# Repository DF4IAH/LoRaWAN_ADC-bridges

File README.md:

# LoRaWAN_ADC-bridges
MCU board as __LoRaWAN TTN device__  for multiple electronic scales.

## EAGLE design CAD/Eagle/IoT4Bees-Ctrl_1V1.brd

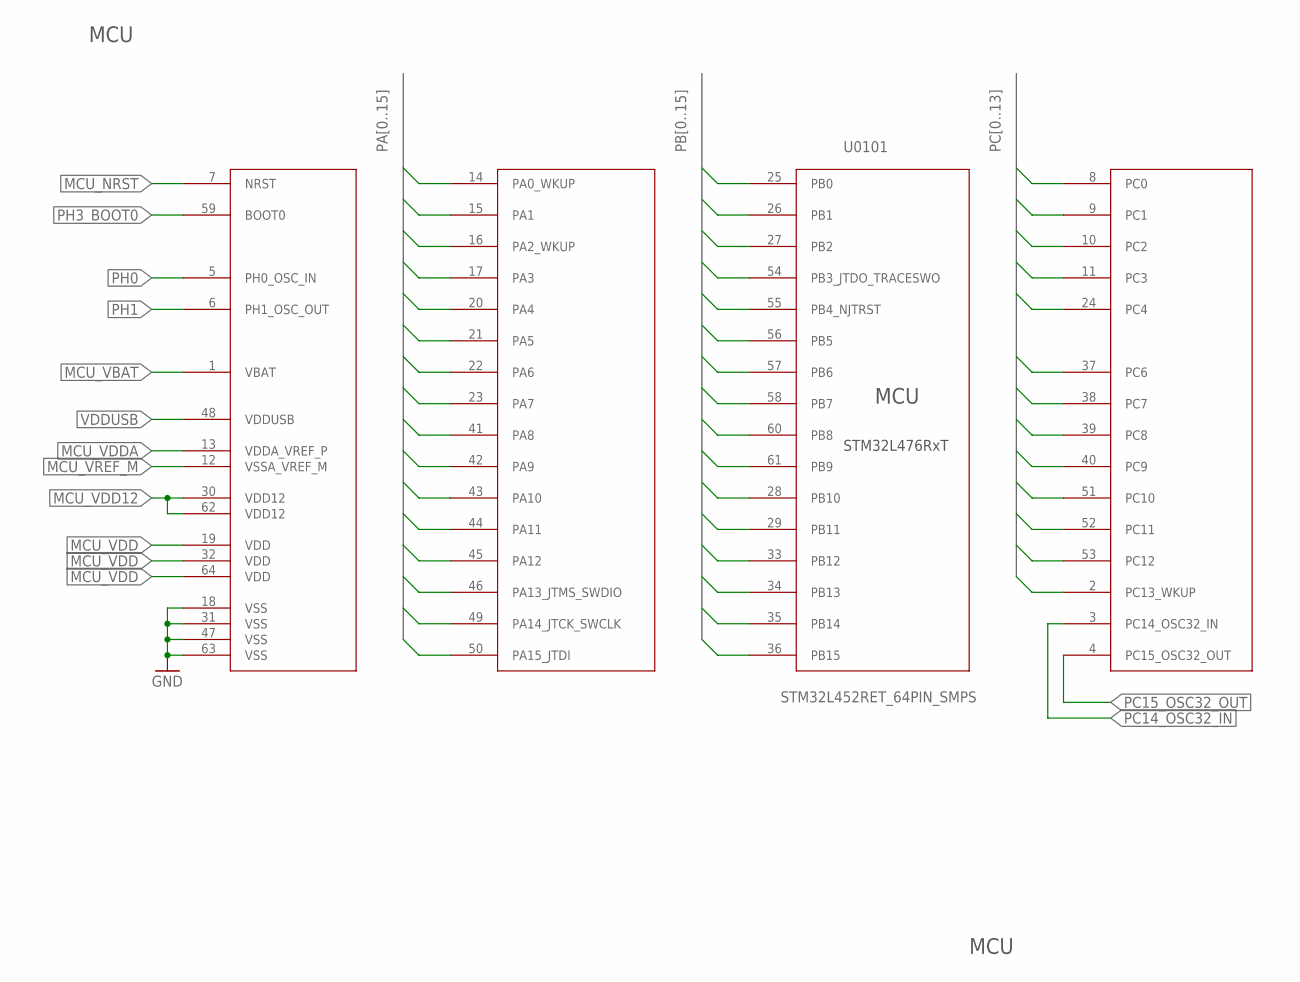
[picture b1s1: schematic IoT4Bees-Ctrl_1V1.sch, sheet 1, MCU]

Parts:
U0101: STM32L452RET_64PIN_SMPS; LQFP64

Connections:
GND: U0101.18 (VSS), U0101.31 (VSS), U0101.47 (VSS), U0101.63 (VSS); also elsewhere on the board
MCU_NRST: U0101.7 (NRST); also elsewhere on the board
MCU_VBAT: U0101.1 (VBAT); also elsewhere on the board
MCU_VDD: U0101.19 (VDD), U0101.32 (VDD), U0101.64 (VDD); also elsewhere on the board
MCU_VDD12: U0101.30 (VDD12), U0101.62 (VDD12); also elsewhere on the board
MCU_VDDA: U0101.13 (VDDA_VREF_P); also elsewhere on the board
MCU_VREF_M: U0101.12 (VSSA_VREF_M); also elsewhere on the board
PA0: U0101.14 (PA0_WKUP); also elsewhere on the board
PA1: U0101.15 (PA1); also elsewhere on the board
PA2: U0101.16 (PA2_WKUP); also elsewhere on the board
PA3: U0101.17 (PA3)
PA4: U0101.20 (PA4); also elsewhere on the board
PA5: U0101.21 (PA5); also elsewhere on the board
PA6: U0101.22 (PA6); also elsewhere on the board
PA7: U0101.23 (PA7); also elsewhere on the board
PA8: U0101.41 (PA8); also elsewhere on the board
PA9: U0101.42 (PA9); also elsewhere on the board
PA10: U0101.43 (PA10); also elsewhere on the board
PA11: U0101.44 (PA11); also elsewhere on the board
PA12: U0101.45 (PA12); also elsewhere on the board
PA13: U0101.46 (PA13_JTMS_SWDIO); also elsewhere on the board
PA14: U0101.49 (PA14_JTCK_SWCLK); also elsewhere on the board
PA15: U0101.50 (PA15_JTDI)
PB0: U0101.25 (PB0)
PB1: U0101.26 (PB1); also elsewhere on the board
PB2: U0101.27 (PB2)
PB3: U0101.54 (PB3_JTDO_TRACESWO)
PB4: U0101.55 (PB4_NJTRST)
PB5: U0101.56 (PB5); also elsewhere on the board
PB6: U0101.57 (PB6); also elsewhere on the board
PB7: U0101.58 (PB7); also elsewhere on the board
PB8: U0101.60 (PB8); also elsewhere on the board
PB9: U0101.61 (PB9)
PB10: U0101.28 (PB10); also elsewhere on the board
PB11: U0101.29 (PB11); also elsewhere on the board
PB12: U0101.33 (PB12); also elsewhere on the board
PB13: U0101.34 (PB13); also elsewhere on the board
PB14: U0101.35 (PB14); also elsewhere on the board
PB15: U0101.36 (PB15); also elsewhere on the board
PC0: U0101.8 (PC0); also elsewhere on the board
PC1: U0101.9 (PC1); also elsewhere on the board
PC2: U0101.10 (PC2); also elsewhere on the board
PC3: U0101.11 (PC3); also elsewhere on the board
PC4: U0101.24 (PC4); also elsewhere on the board
PC6: U0101.37 (PC6)
PC7: U0101.38 (PC7); also elsewhere on the board
PC8: U0101.39 (PC8); also elsewhere on the board
PC9: U0101.40 (PC9); also elsewhere on the board
PC10: U0101.51 (PC10); also elsewhere on the board
PC11: U0101.52 (PC11); also elsewhere on the board
PC12: U0101.53 (PC12); also elsewhere on the board
PC13: U0101.2 (PC13_WKUP); also elsewhere on the board
PC14_OSC32_IN: U0101.3 (PC14_OSC32_IN); also elsewhere on the board
PC15_OSC32_OUT: U0101.4 (PC15_OSC32_OUT); also elsewhere on the board
PH0: U0101.5 (PH0_OSC_IN); also elsewhere on the board
PH1: U0101.6 (PH1_OSC_OUT); also elsewhere on the board
PH3_BOOT0: U0101.59 (BOOT0); also elsewhere on the board
VDDUSB: U0101.48 (VDDUSB); also elsewhere on the board

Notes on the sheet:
STM32L476RxT
MCU

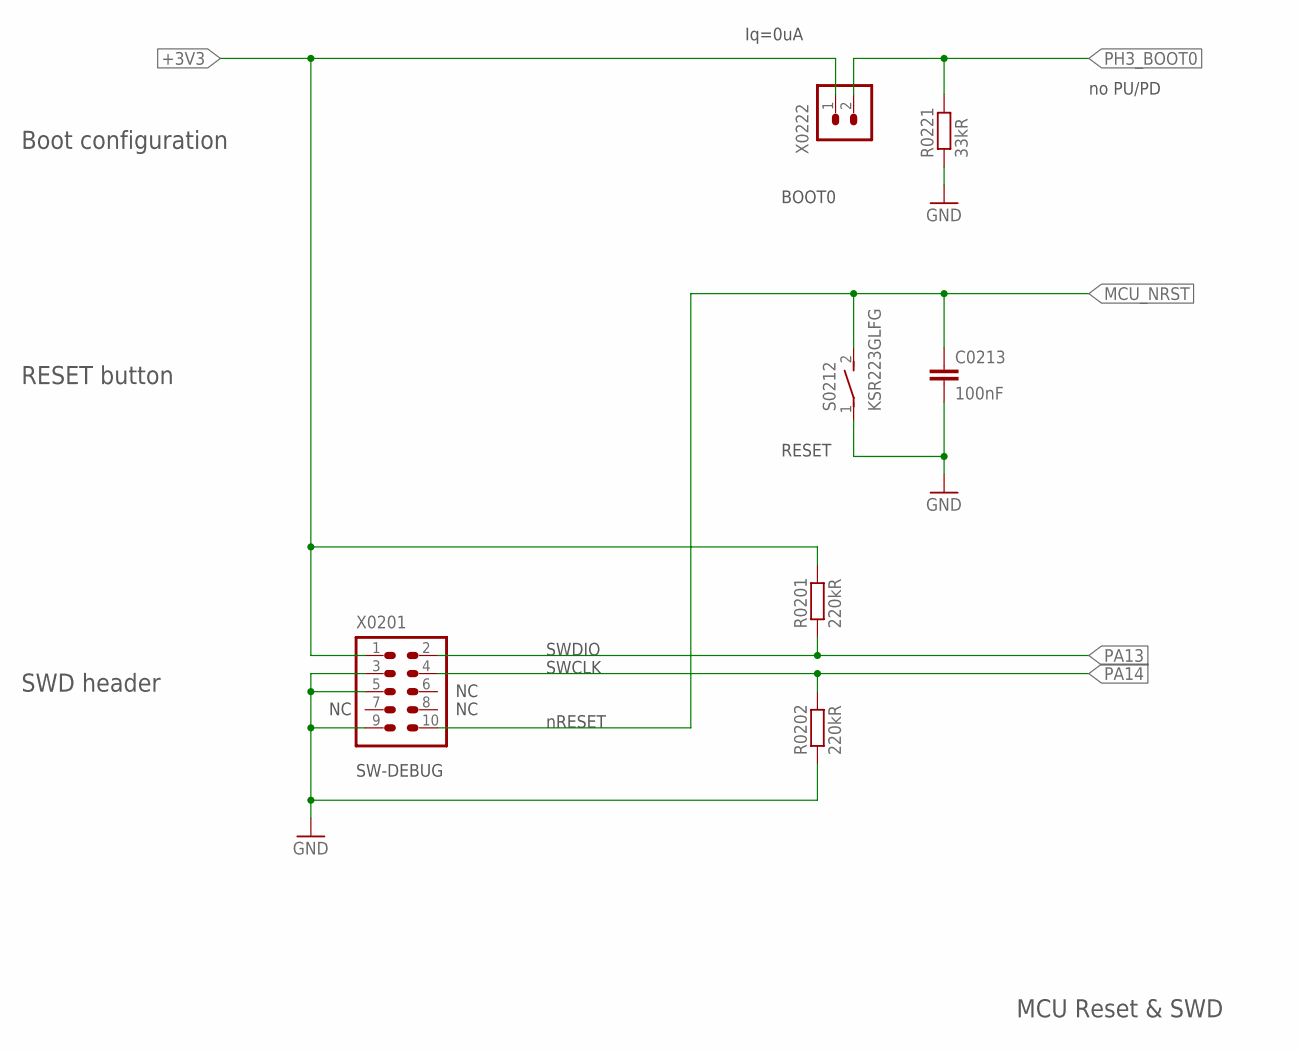
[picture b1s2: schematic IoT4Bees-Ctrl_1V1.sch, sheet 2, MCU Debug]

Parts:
C0213: 100nF; C0402
R0201, R0202: 220kR; R0402
R0221: 33kR; R0402
S0212: KSR223GLFG; KSR223G_SMD_1POL
X0201: FTSH-105-01-F-D-K; 2X05_1MM27_SHROUDED_CORTEX_JTAG_SWD
X0222: HEADER-1X2; 1X02

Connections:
+3V3: R0201.2, X0201.1, X0222.1; also elsewhere on the board
GND: C0213.2, R0202.1, R0221.1, S0212.1, X0201.3, X0201.5, X0201.9; also elsewhere on the board
MCU_NRST: C0213.1, S0212.2 (S), X0201.10; also elsewhere on the board
PA13: R0201.1, X0201.2; also elsewhere on the board
PA14: R0202.2, X0201.4; also elsewhere on the board
PH3_BOOT0: R0221.2, X0222.2; also elsewhere on the board

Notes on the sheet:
SWDIO
SWCLK
RESET
BOOT0
SW-DEBUG
SWD header
Boot configuration
RESET button
nRESET
MCU Reset & SWD
no PU/PD
Iq=0uA

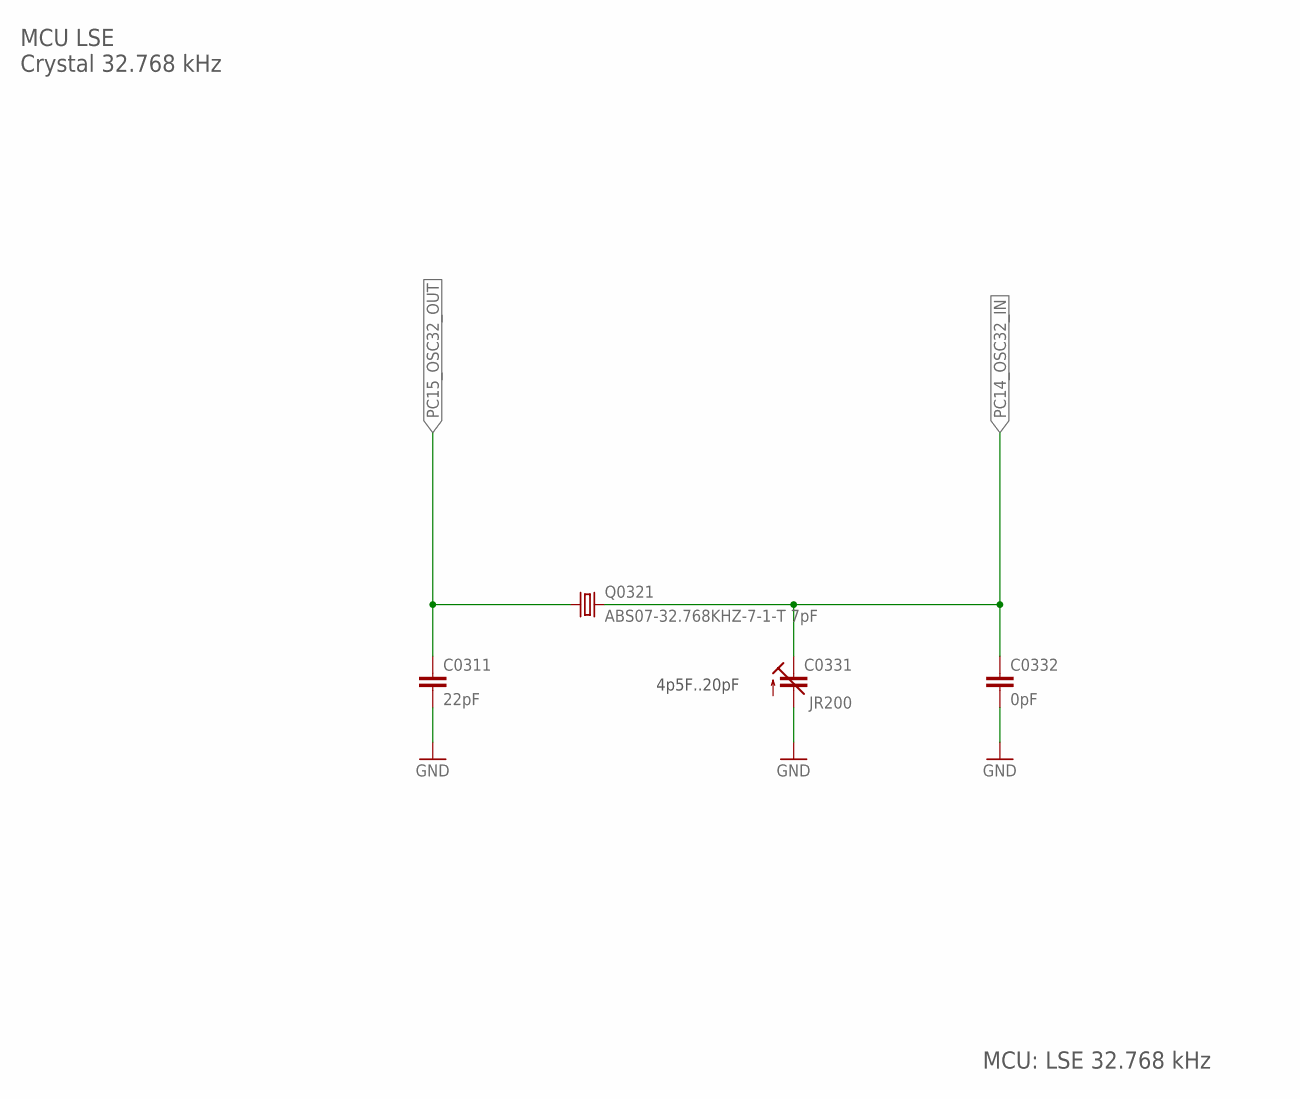
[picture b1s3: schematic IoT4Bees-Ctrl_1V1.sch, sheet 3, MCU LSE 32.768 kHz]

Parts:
C0311: 22pF; C0402
C0331: JR200; 3MM2_X_2MM5
C0332: 0pF; C0402
Q0321: ABS07-32.768KHZ-7-1-T 7pF; ABS07

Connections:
GND: C0311.2, C0331.+ (A), C0332.2; also elsewhere on the board
PC14_OSC32_IN: C0331.- (E), C0332.1, Q0321.2; also elsewhere on the board
PC15_OSC32_OUT: C0311.1, Q0321.1; also elsewhere on the board

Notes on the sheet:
4p5F..20pF
MCU LSE Crystal 32.768 kHz
MCU: LSE 32.768 kHz

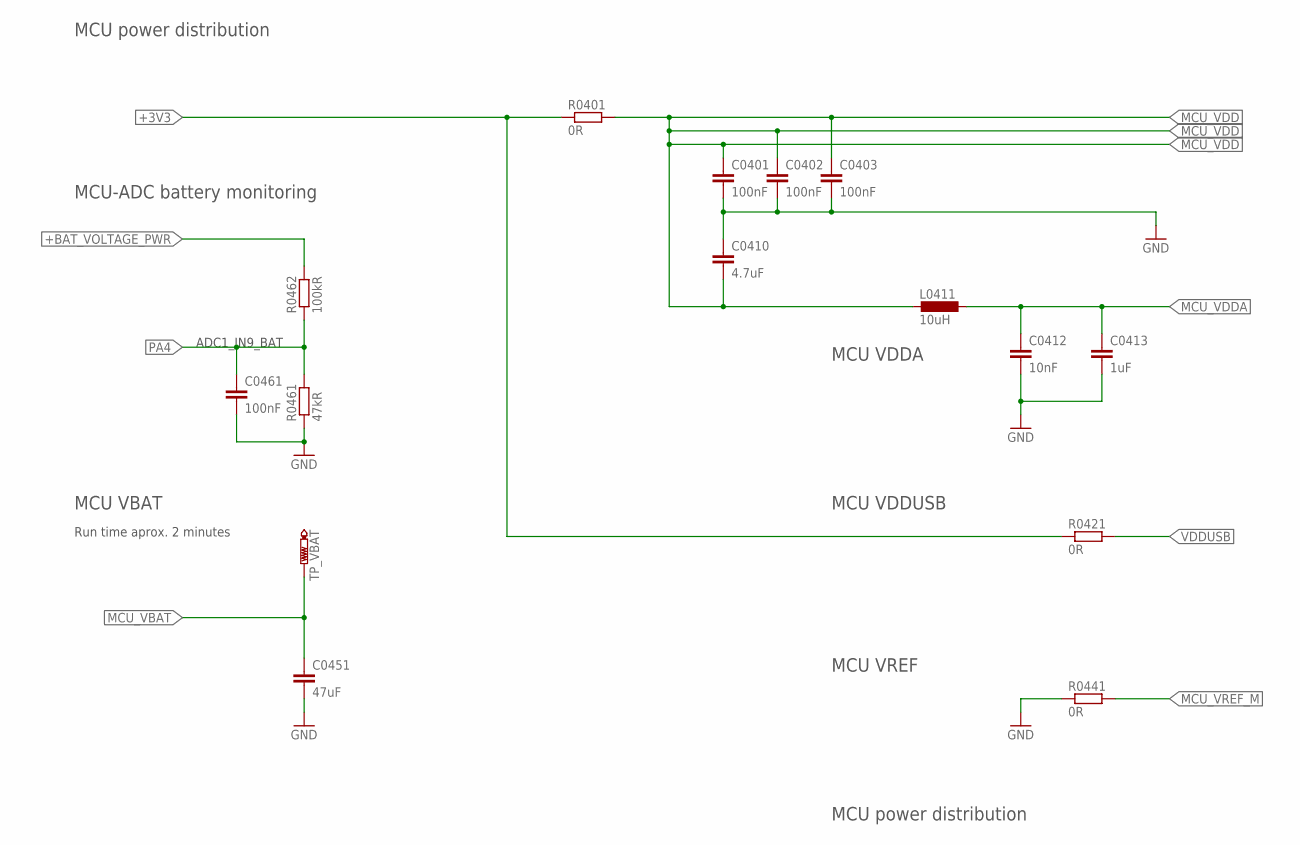
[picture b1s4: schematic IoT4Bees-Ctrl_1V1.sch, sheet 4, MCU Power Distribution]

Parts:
C0401, C0402, C0403, C0461: 100nF; C0402
C0410: 4.7uF; C0603
C0412: 10nF; C0402
C0413: 1uF; C0402
C0451: 47uF; C0805
L0411: 10uH; L0603
R0401, R0421, R0441: 0R; R0402
R0461: 47kR; R0402
R0462: 100kR; R0402
TP_VBAT: PTR1TP06R; TP06R

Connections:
+3V3: R0401.1, R0421.1; also elsewhere on the board
+BAT_VOLTAGE_PWR: R0462.2; also elsewhere on the board
GND: C0401.2, C0402.2, C0403.2, C0410.1, C0412.2, C0413.2, C0451.2, C0461.2, R0441.1, R0461.1; also elsewhere on the board
MCU_VBAT: C0451.1, TP_VBAT.TP; also elsewhere on the board
MCU_VDD: C0401.1, C0402.1, C0403.1, C0410.2, L0411.1, R0401.2; also elsewhere on the board
MCU_VDDA: C0412.1, C0413.1, L0411.2; also elsewhere on the board
MCU_VREF_M: R0441.2; also elsewhere on the board
PA4: C0461.1, R0461.2, R0462.1; also elsewhere on the board
VDDUSB: R0421.2; also elsewhere on the board

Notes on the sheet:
MCU VDDA
MCU VREF
MCU VBAT
MCU power distribution
Run time aprox. 2 minutes
ADC1_IN9_BAT
MCU-ADC battery monitoring
MCU VDDUSB

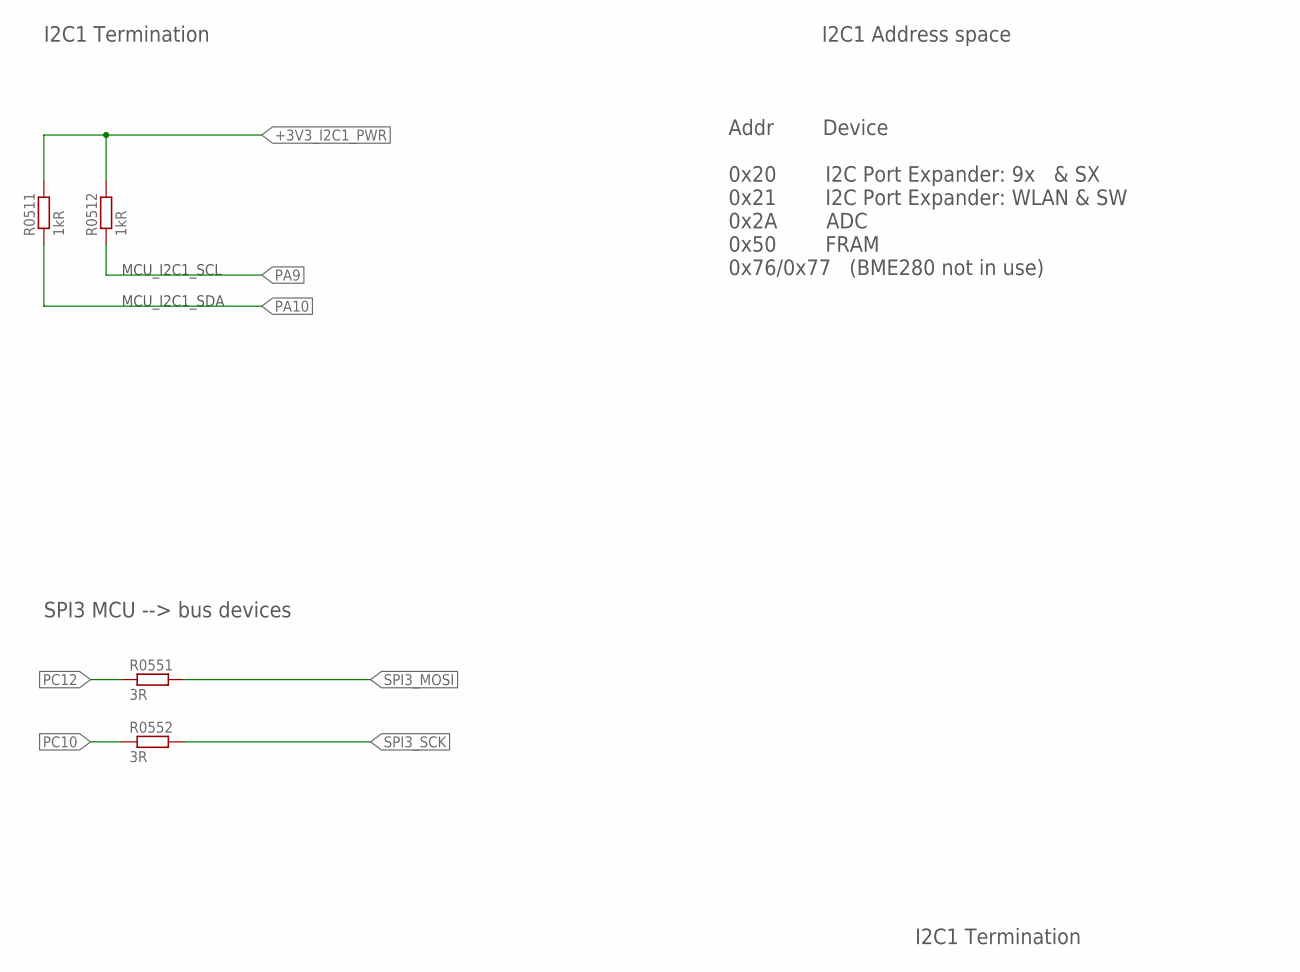
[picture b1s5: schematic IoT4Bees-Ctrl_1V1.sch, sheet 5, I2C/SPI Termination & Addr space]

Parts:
R0511, R0512: 1kR; R0402
R0551, R0552: 3R; R0402

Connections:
+3V3_I2C1_PWR: R0511.2, R0512.2; also elsewhere on the board
PA9: R0512.1; also elsewhere on the board
PA10: R0511.1; also elsewhere on the board
PC10: R0552.1; also elsewhere on the board
PC12: R0551.1; also elsewhere on the board
SPI3_MOSI: R0551.2; also elsewhere on the board
SPI3_SCK: R0552.2; also elsewhere on the board

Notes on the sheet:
Addr Device 0x20 I2C Port Expander: 9x & SX 0x21 I2C Port Expander: WLAN & SW 0x2A ADC 0x50 FRAM 0x76/0x77 (BME280 not in use)
I2C1 Termination
I2C1 Address space
MCU_I2C1_SCL
MCU_I2C1_SDA
SPI3 MCU --> bus devices

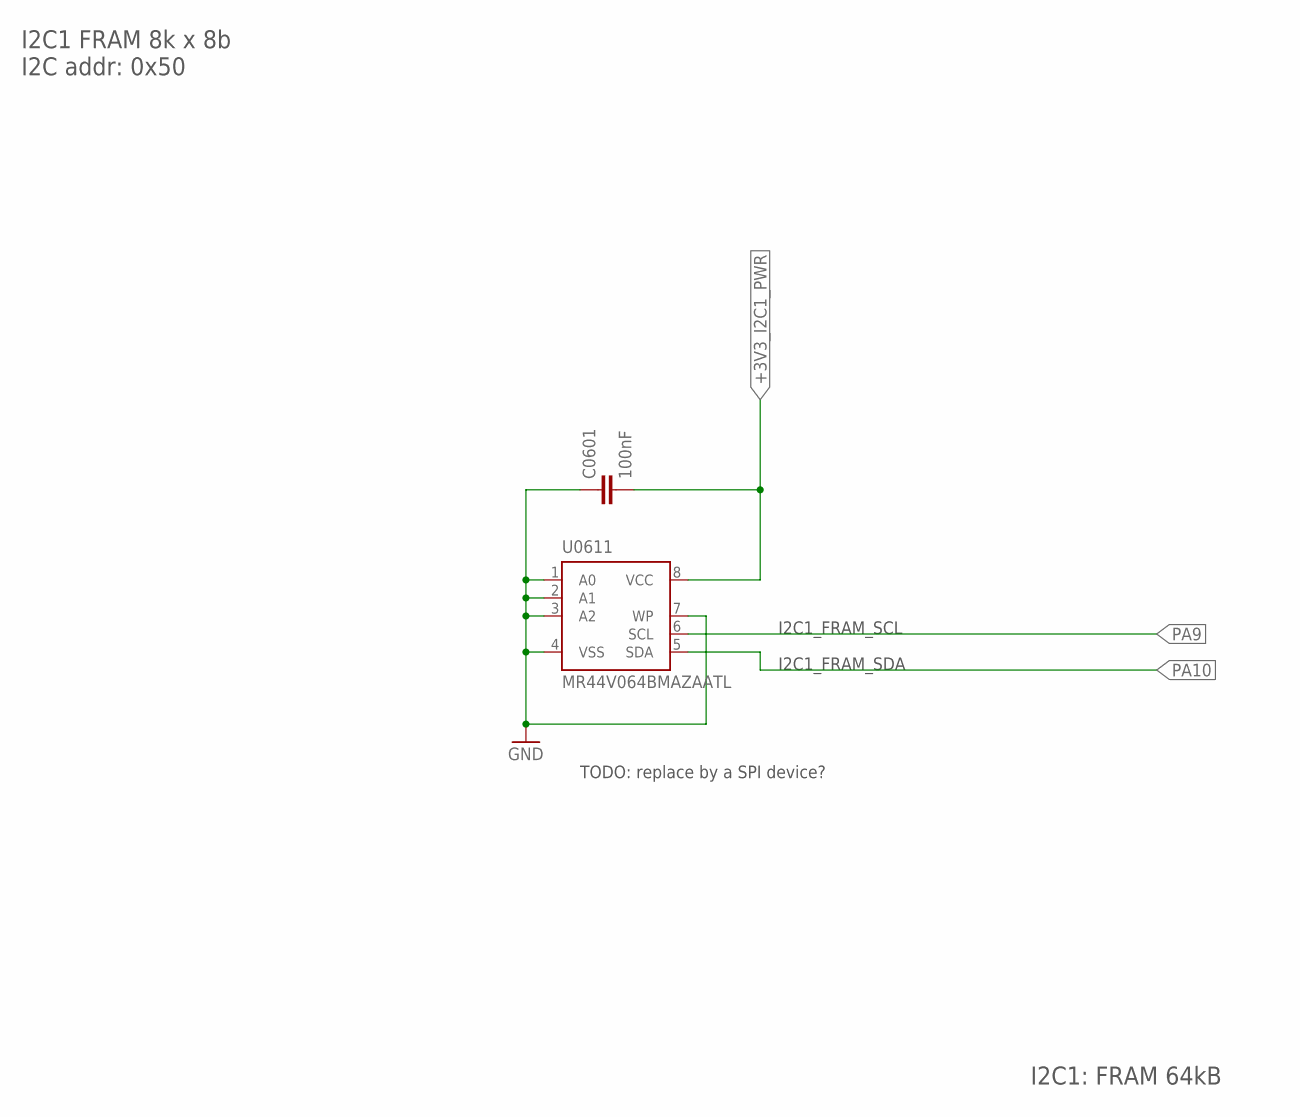
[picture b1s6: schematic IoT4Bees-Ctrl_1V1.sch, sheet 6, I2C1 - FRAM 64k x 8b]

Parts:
C0601: 100nF; C0402
U0611: MR44V064BMAZAATL; SOIC8_150MIL

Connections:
+3V3_I2C1_PWR: C0601.2, U0611.8 (VCC); also elsewhere on the board
GND: C0601.1, U0611.1 (A0), U0611.2 (A1), U0611.3 (A2), U0611.4 (VSS), U0611.7 (WP); also elsewhere on the board
PA9: U0611.6 (SCL); also elsewhere on the board
PA10: U0611.5 (SDA); also elsewhere on the board

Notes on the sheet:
I2C1: FRAM 64kB
I2C1 FRAM 8k x 8b I2C addr: 0x50
I2C1_FRAM_SCL
I2C1_FRAM_SDA
TODO: replace by a SPI device?

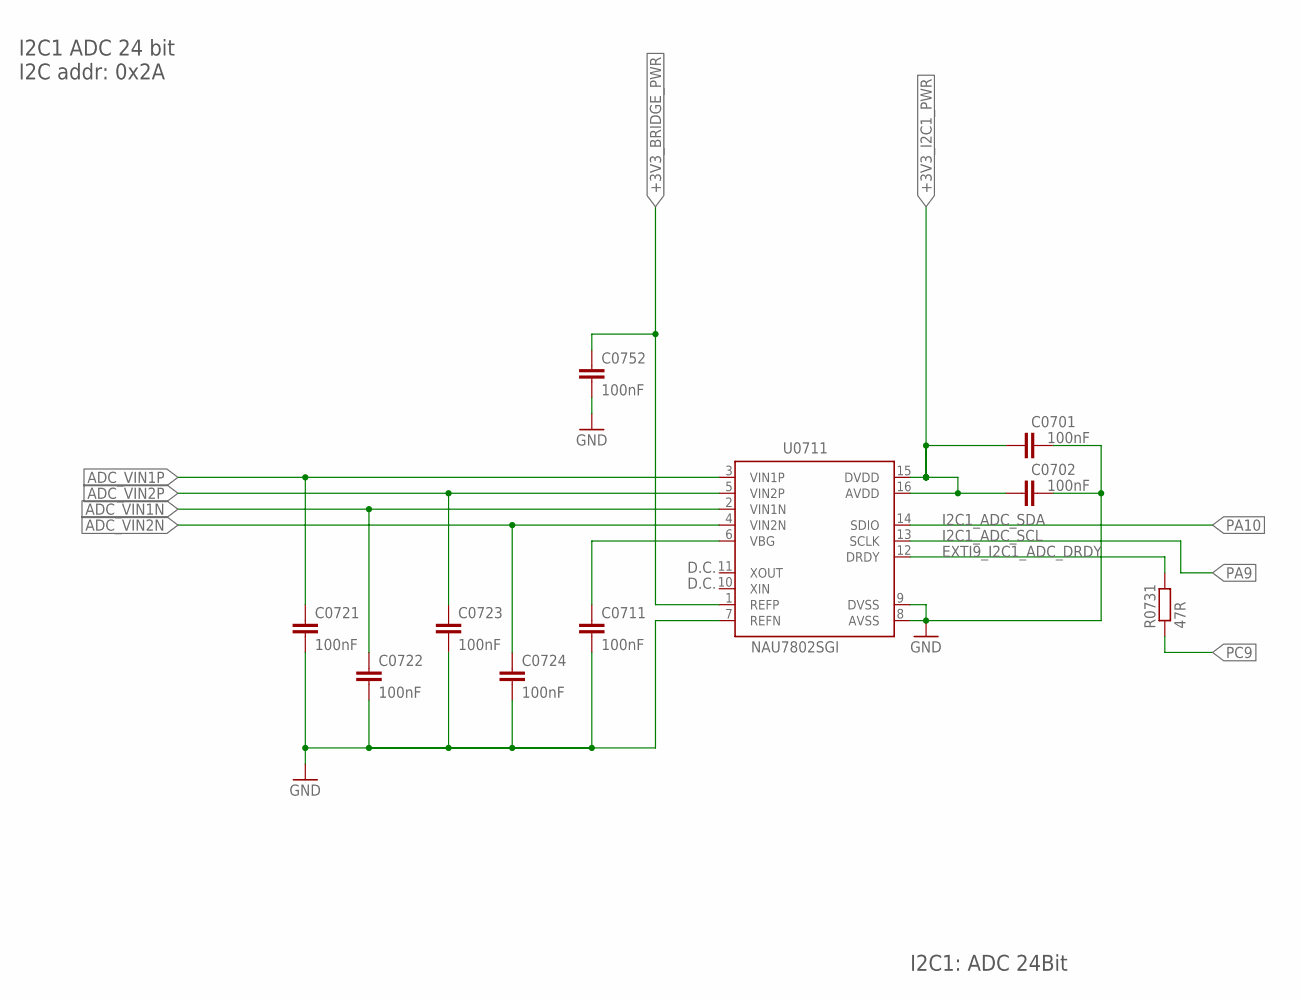
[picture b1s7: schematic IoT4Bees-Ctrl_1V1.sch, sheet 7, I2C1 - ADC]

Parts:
C0701, C0702, C0711, C0721, C0722, C0723, C0724, C0752: 100nF; C0402
R0731: 47R; R0402
U0711: NAU7802SGI; LSOP16

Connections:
+3V3_BRIDGE_PWR: C0752.1, U0711.1 (REFP); also elsewhere on the board
+3V3_I2C1_PWR: C0701.1, C0702.1, U0711.15 (DVDD), U0711.16 (AVDD); also elsewhere on the board
ADC_VBG: C0711.1, U0711.6 (VBG)
ADC_VIN1N: C0722.1, U0711.2 (VIN1N); also elsewhere on the board
ADC_VIN1P: C0721.1, U0711.3 (VIN1P); also elsewhere on the board
ADC_VIN2N: C0724.1, U0711.4 (VIN2N); also elsewhere on the board
ADC_VIN2P: C0723.1, U0711.5 (VIN2P); also elsewhere on the board
EXTI9_I2C1_ADC_DRDY: R0731.2, U0711.12 (DRDY)
GND: C0701.2, C0702.2, C0711.2, C0721.2, C0722.2, C0723.2, C0724.2, C0752.2, U0711.7 (REFN), U0711.8 (AVSS), U0711.9 (DVSS); also elsewhere on the board
PA9: U0711.13 (SCLK); also elsewhere on the board
PA10: U0711.14 (SDIO); also elsewhere on the board
PC9: R0731.1; also elsewhere on the board

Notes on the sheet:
I2C1: ADC 24Bit
I2C1 ADC 24 bit I2C addr: 0x2A
I2C1_ADC_SDA
I2C1_ADC_SCL
D.C.

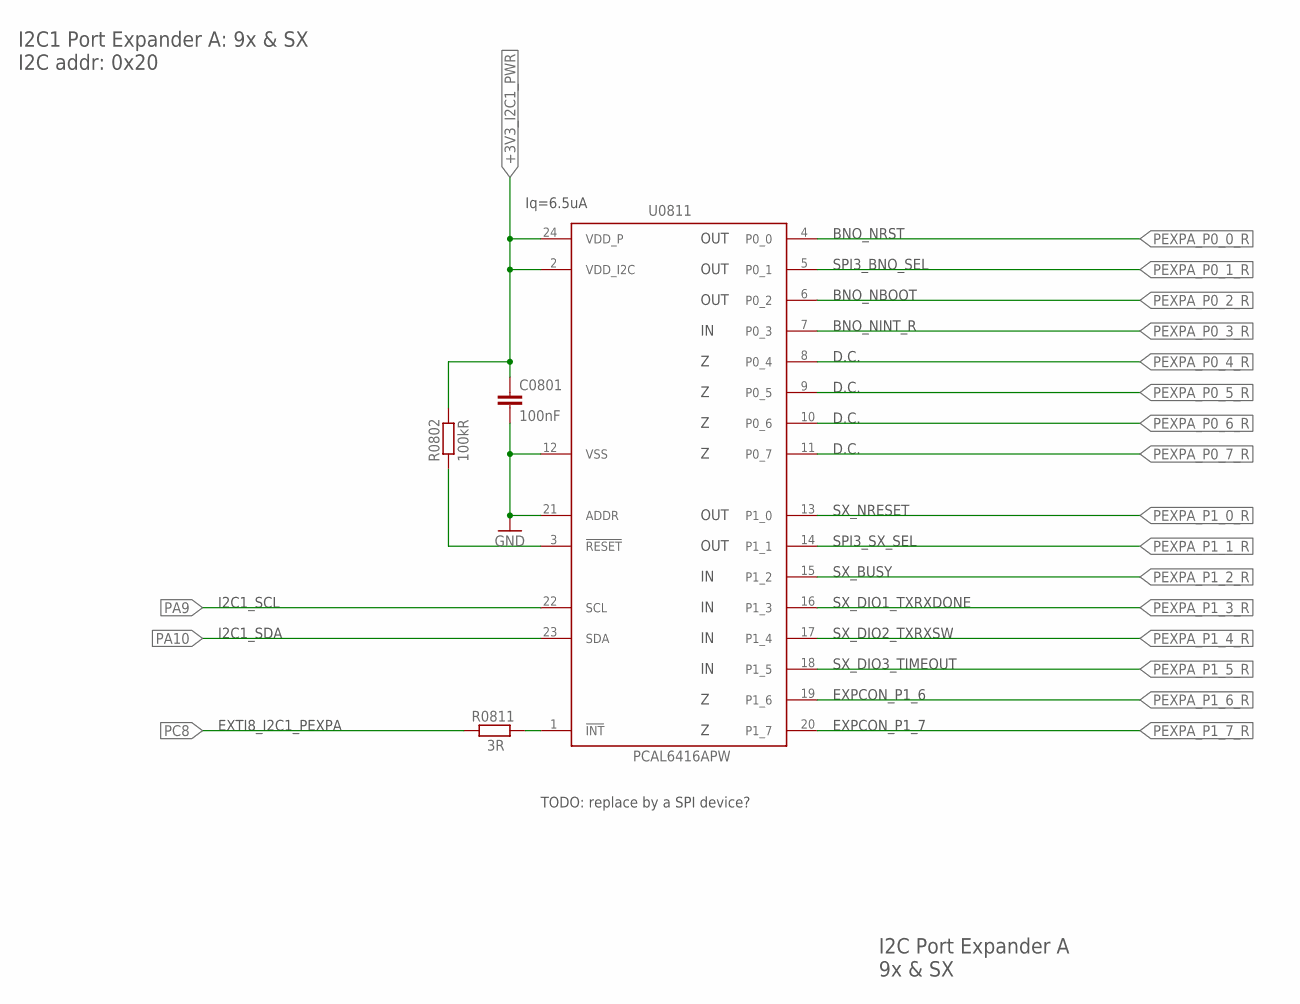
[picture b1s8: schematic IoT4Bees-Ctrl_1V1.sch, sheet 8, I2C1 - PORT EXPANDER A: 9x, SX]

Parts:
C0801: 100nF; C0402
R0802: 100kR; R0402
R0811: 3R; R0402
U0811: PCAL6416APW; TSSOP24_SOT355-1

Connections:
+3V3_I2C1_PWR: C0801.1, R0802.2, U0811.2 (VDD_I2C), U0811.24 (VDD_P); also elsewhere on the board
GND: C0801.2, U0811.12 (VSS), U0811.21 (ADDR); also elsewhere on the board
PA9: U0811.22 (SCL); also elsewhere on the board
PA10: U0811.23 (SDA); also elsewhere on the board
PC8: R0811.1; also elsewhere on the board
PEXPA_INTN: R0811.2, U0811.1 (!INT)
PEXPA_P0_0_R: U0811.4 (P0_0); also elsewhere on the board
PEXPA_P0_1_R: U0811.5 (P0_1); also elsewhere on the board
PEXPA_P0_2_R: U0811.6 (P0_2); also elsewhere on the board
PEXPA_P0_3_R: U0811.7 (P0_3); also elsewhere on the board
PEXPA_P0_4_R: U0811.8 (P0_4)
PEXPA_P0_5_R: U0811.9 (P0_5)
PEXPA_P0_6_R: U0811.10 (P0_6)
PEXPA_P0_7_R: U0811.11 (P0_7)
PEXPA_P1_0_R: U0811.13 (P1_0); also elsewhere on the board
PEXPA_P1_1_R: U0811.14 (P1_1); also elsewhere on the board
PEXPA_P1_2_R: U0811.15 (P1_2); also elsewhere on the board
PEXPA_P1_3_R: U0811.16 (P1_3); also elsewhere on the board
PEXPA_P1_4_R: U0811.17 (P1_4); also elsewhere on the board
PEXPA_P1_5_R: U0811.18 (P1_5); also elsewhere on the board
PEXPA_P1_6_R: U0811.19 (P1_6); also elsewhere on the board
PEXPA_P1_7_R: U0811.20 (P1_7); also elsewhere on the board
PEXPA_RESET: R0802.1, U0811.3 (!RESET)

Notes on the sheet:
I2C Port Expander A 9x & SX
I2C1 Port Expander A: 9x & SX I2C addr: 0x20
Iq=6.5uA
EXTI8_I2C1_PEXPA
D.C.
OUT
BNO_NRST
BNO_NBOOT
SPI3_BNO_SEL
BNO_NINT_R
SX_BUSY
SX_NRESET
SPI3_SX_SEL
SX_DIO3_TIMEOUT
SX_DIO2_TXRXSW
SX_DIO1_TXRXDONE
EXPCON_P1_6
I2C1_SCL
I2C1_SDA
EXPCON_P1_7
TODO: replace by a SPI device?

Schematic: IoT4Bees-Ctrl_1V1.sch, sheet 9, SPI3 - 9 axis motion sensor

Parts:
C0901, C0902, C0903: 100nF; C0402
C0921, C0922: 22pF; C0402
D0901: CMAD6001; SOD923
Q0921: ABS07-32.768KHZ; ABS07
R0901, R0902, R0904: 3R; R0402
R0903: 47R; R0402
R0931, R0932: 3.9kR; R0402
U0911: BNO085; BNO085_LGA28

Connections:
+3V3_SPI3_PWR: C0901.1, C0902.1, R0931.2, R0932.2, U0911.3 (VDD), U0911.5 (PS1), U0911.28 (VDDIO); also elsewhere on the board
BNO085_PS0_WAKE_R: D0901.A, R0903.1
BNO_CAP: C0903.1, U0911.9 (CAP)
BNO_CLKSEL1_XOUT32: C0922.1, Q0921.1, U0911.26 (CLKSEL1/XOUT32)
BNO_ENV_SCL: R0932.1, U0911.15 (ENV_SCL)
BNO_ENV_SDA: R0931.1, U0911.16 (ENV_SDA)
BNO_H_CSN: R0904.2, U0911.18 (H_CSN)
BNO_INTN: R0902.2, U0911.14 (H_INTN)
BNO_MISO: R0901.2, U0911.20 (H_SDA/MISO/TX)
BNO_PS0_WAKE: R0903.2, U0911.6 (PS0/WAKE)
BNO_XIN32: C0921.1, Q0921.2, U0911.27 (XIN32)
GND: C0901.2, C0902.2, C0903.2, C0921.2, C0922.2, U0911.2 (VSS), U0911.10 (CLKSEL0), U0911.25 (VSSIO); also elsewhere on the board
PC11: R0901.1; also elsewhere on the board
PC13: D0901.C; also elsewhere on the board
PEXPA_P0_0_R: U0911.11 (NRST); also elsewhere on the board
PEXPA_P0_1_R: R0904.1; also elsewhere on the board
PEXPA_P0_2_R: U0911.4 (BOOTN); also elsewhere on the board
PEXPA_P0_3_R: R0902.1; also elsewhere on the board
SPI3_MOSI: U0911.17 (SA0/H_MOSI); also elsewhere on the board
SPI3_SCK: U0911.19 (H_SCL/SCL/RX); also elsewhere on the board

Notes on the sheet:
9-axis sensor: BNO-085 SPI
BNO_NINT_R
Position tracking
SPI3_BNO_MISO_R
BNO_NBOOT
BOARD_WKUP
BNO_NRST
SPI3_BNO_SEL
Iq=130uA

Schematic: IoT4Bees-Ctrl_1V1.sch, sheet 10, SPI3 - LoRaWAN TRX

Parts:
C1001: 10uF; C0603
C1002, C1006: 10nF; C0402
C1003: 470nF; C0402
C1004: 47pF; C0402
C1005: 47nF; C0402
C1063, C1066: 3.3pF; C0402
C1064: 22pF; C0402
C1065: 1.8pF; C0402
C1067: 0.0pF; C0402
C1071, C1072: 1nF; C0402
C1081: 33pF; C0402
C1082, C1091: 2.7pF; C0402
C1083: 2.2pF; C0402
C1092: 3.8pF; C0402
C1093: 0pF; C0402
L1001: 15uH; L0805
L1002, L1062: 47nH; L0603
L1063: 2.2nH; L0603
L1064: 1.5nH; L0603
L1082: 6.8nH; L0603
L1091: 13nH; L0603
Q1011: ABM3B-32.0000MHZ; ABM3B
R1011, R1021, R1024: 3R; R0402
R1051, R1052, R1053, R1071: 47R; R0402
TP_SX_DIO1, TP_SX_DIO2, TP_SX_DIO3: PTR1TP06R; TP06R
U1001: SX1261IMLTRT; QFN24-4X4-0P5-PAD
U1071: PE4259; SC-70_6-LEAD_2X1MM25_0P65
X1081: ANTENNATINY; SMA_UFL_PAD_TINY

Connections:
+3V3_SPI3_PWR: C1001.1, C1002.1, R1071.2, U1001.10 (VBAT), U1001.11 (VBAT_IO); also elsewhere on the board
ANT_LORA: C1083.2, L1082.1, X1081.ANT1 (SIGNAL), X1081.ANT2 (SIGNAL), X1081.ANT3 (SIGNAL)
GND: C1001.2, C1002.2, C1003.2, C1004.2, C1005.2, C1006.1, C1065.1, C1066.2, C1067.2, C1071.2, C1072.2, C1082.1, C1083.1, C1091.1, C1093.1, Q1011.2 (3), Q1011.4 (3), U1001.2 (VSS), U1001.5 (VSS), U1001.8 (VSS), U1001.20 (VSS), U1001.25 (VSS), U1071.2 (GND), X1081.GND1 (GND), X1081.GND2 (GND), X1081.GND3 (GND), X1081.GND4 (GND); also elsewhere on the board
MCU_SX_SEL_OUT: R1021.2, U1001.19 (NSS)
PC11: R1024.1; also elsewhere on the board
PEXPA_P1_0_R: U1001.15 (NRESET); also elsewhere on the board
PEXPA_P1_1_R: R1021.1; also elsewhere on the board
PEXPA_P1_2_R: R1011.1; also elsewhere on the board
PEXPA_P1_3_R: R1053.2; also elsewhere on the board
PEXPA_P1_4_R: C1072.1, R1052.2, U1071.4 (CTRL); also elsewhere on the board
PEXPA_P1_5_R: R1051.2; also elsewhere on the board
PE_!CTRL: C1071.1, R1071.1, U1071.6 (VDD_!CTRL)
PE_RFC: C1081.1, U1071.5 (RFC)
PE_RFC_2: C1081.2, C1082.2, L1082.2
SPI3_MOSI: U1001.17 (MOSI); also elsewhere on the board
SPI3_SCK: U1001.18 (SCLK); also elsewhere on the board
SX_BUSY: R1011.2, U1001.14 (BUSY)
SX_DCC_SW: L1001.1, U1001.9 (DCC_SW)
SX_DIO1: R1053.1, TP_SX_DIO1.TP, U1001.13 (DIO1)
SX_DIO2: R1052.1, TP_SX_DIO2.TP, U1001.12 (DIO2)
SX_DIO3: R1051.1, TP_SX_DIO3.TP, U1001.6 (DIO3)
SX_MISO: R1024.2, U1001.16 (MISO)
SX_RFI_2: C1092.2, C1093.2, U1071.3 (RF2)
SX_RFI_N: C1092.1, L1091.1, U1001.22 (RFI_N)
SX_RFI_P: C1091.2, L1091.2, U1001.21 (RFI_P)
SX_RFO: C1063.1, C1065.2, L1062.1, L1063.2, U1001.23 (RFO)
SX_RFO_3: C1063.2, C1064.1, C1066.1, L1063.1
SX_RFO_4: C1064.2, L1064.2
SX_RFO_5: C1067.1, L1064.1, U1071.1 (RF1)
SX_VDD_IN: C1006.2, L1002.1, U1001.1 (VDD_IN)
SX_VREG: C1003.1, L1001.2, L1002.2, U1001.7 (VREG)
SX_VR_PA: C1004.1, C1005.1, L1062.2, U1001.24 (VR_PA)
SX_XTA: Q1011.1, U1001.3 (XTA)
SX_XTB: Q1011.3 (2), U1001.4 (XTB)

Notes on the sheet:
SPI3: SX1261
SPI3 LoRaWAN TRX SX1261
SX_NRESET
SX_BUSY
SX_DIO2_TXRXSW
SX_DIO3_TIMEOUT
SX_DIO1_TXRXDONE
Iq=1.2uA
SPI3_SX_MISO
SPI3_SX_SEL
X1081
HI = TX LO = RX
SX_PE_VDD

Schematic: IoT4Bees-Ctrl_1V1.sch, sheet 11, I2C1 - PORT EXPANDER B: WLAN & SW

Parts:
C1113: 100nF; C0402
R1111: 3R; R0402
R1112: 100kR; R0402
U1111: PCAL6416APW; TSSOP24_SOT355-1

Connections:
+3V3_I2C1_PWR: C1113.1, R1112.2, U1111.2 (VDD_I2C), U1111.21 (ADDR), U1111.24 (VDD_P); also elsewhere on the board
GND: C1113.2, U1111.12 (VSS); also elsewhere on the board
PA9: U1111.22 (SCL); also elsewhere on the board
PA10: U1111.23 (SDA); also elsewhere on the board
PC7: R1111.1; also elsewhere on the board
PEXPB_INTN: R1111.2, U1111.1 (!INT)
PEXPB_P0_0_R: U1111.4 (P0_0)
PEXPB_P0_1_R: U1111.5 (P0_1); also elsewhere on the board
PEXPB_P0_2_R: U1111.6 (P0_2); also elsewhere on the board
PEXPB_P0_3_R: U1111.7 (P0_3); also elsewhere on the board
PEXPB_P0_4_R: U1111.8 (P0_4); also elsewhere on the board
PEXPB_P0_5_R: U1111.9 (P0_5); also elsewhere on the board
PEXPB_P0_6_R: U1111.10 (P0_6); also elsewhere on the board
PEXPB_P0_7_R: U1111.11 (P0_7); also elsewhere on the board
PEXPB_P1_0_R: U1111.13 (P1_0); also elsewhere on the board
PEXPB_P1_1_R: U1111.14 (P1_1); also elsewhere on the board
PEXPB_P1_2_R: U1111.15 (P1_2); also elsewhere on the board
PEXPB_P1_3_R: U1111.16 (P1_3); also elsewhere on the board
PEXPB_P1_4_R: U1111.17 (P1_4); also elsewhere on the board
PEXPB_P1_5_R: U1111.18 (P1_5); also elsewhere on the board
PEXPB_P1_6_R: U1111.19 (P1_6); also elsewhere on the board
PEXPB_P1_7_R: U1111.20 (P1_7); also elsewhere on the board
PEXPB_RESET: R1112.1, U1111.3 (!RESET)

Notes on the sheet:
I2C Port Expander B WLAN & SW
I2C1 Port Expander B: WLAN & SW I2C addr: 0x21
Iq=6.5uA
EXTI7_I2C1_PEXPB
D.C.
ESP_RST_R
ESP_GPIO10_R
ESP_SCLK_R
ESP_MOSI_R
ESP_GPIO2_R
ESP_GPIO0_R
ESP_GPIO4_R
ESP_GPIO5_R
ESP_CHIP_EN_R
I2C1_SCL
I2C1_SDA
ESP_GPIO9_R
ESP_MISO_R
ESP_CS0_R
ESP_GPIO12_R
ESP_GPIO14_R
ESP_GPIO16_R
OUT
TODO: replace by a SPI device? TODO: to be removed?

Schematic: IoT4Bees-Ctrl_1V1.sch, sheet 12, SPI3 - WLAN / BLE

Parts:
C1201: 10uF; C0603
C1202: 10nF; C0402
R1257, R1266, R1271, R1272: 47R; R0402
U1211: ESP-12F__2P00_24MM-X-16MM

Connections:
+3V3_USART1_PWR: C1201.1, C1202.1, U1211.8 (VCC); also elsewhere on the board
ESP_CTS: R1257.1, U1211.7 (GPIO13_UART0_CTS)
ESP_RTS: R1266.1, U1211.16 (GPIO15_UART0_RTS)
ESP_RX: R1271.1, U1211.21 (RXD)
ESP_TX: R1272.1, U1211.22 (TXD)
GND: C1201.2, C1202.2, U1211.2 (ADC), U1211.15 (VSS); also elsewhere on the board
PA11: R1257.2; also elsewhere on the board
PA12: R1266.2; also elsewhere on the board
PB6: R1271.2; also elsewhere on the board
PB7: R1272.2; also elsewhere on the board
PEXPB_P0_1_R: U1211.1 (RST); also elsewhere on the board
PEXPB_P0_2_R: U1211.3 (EN); also elsewhere on the board
PEXPB_P0_3_R: U1211.4 (GPIO16_WKUP); also elsewhere on the board
PEXPB_P0_4_R: U1211.5 (GPIO14); also elsewhere on the board
PEXPB_P0_5_R: U1211.6 (GPIO12); also elsewhere on the board
PEXPB_P0_6_R: U1211.9 (CS0); also elsewhere on the board
PEXPB_P0_7_R: U1211.10 (MISO); also elsewhere on the board
PEXPB_P1_0_R: U1211.11 (GPIO9); also elsewhere on the board
PEXPB_P1_1_R: U1211.12 (GPIO10); also elsewhere on the board
PEXPB_P1_2_R: U1211.13 (MOSI); also elsewhere on the board
PEXPB_P1_3_R: U1211.14 (SCLK); also elsewhere on the board
PEXPB_P1_4_R: U1211.17 (GPIO2); also elsewhere on the board
PEXPB_P1_5_R: U1211.18 (GPIO0); also elsewhere on the board
PEXPB_P1_6_R: U1211.19 (GPIO4); also elsewhere on the board
PEXPB_P1_7_R: U1211.20 (GPIO5); also elsewhere on the board

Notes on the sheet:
SPI3: WLAN
SPI3 WLAN TRX ESP-12-F (AI-THINKER)
ESP_GPIO5_R
ESP_GPIO4_R
ESP_GPIO0_R
ESP_GPIO2_R
ESP_RTS_R
ESP_CTS_R
ESP_RX_R
ESP_TX_R
ESP_SCLK_R
ESP_MOSI_R
ESP_GPIO10_R
ESP_GPIO9_R
ESP_MISO_R
ESP_CS0_R
ESP_CHIP_EN
ESP_GPIO16
ESP_GPIO14
ESP_GPIO12
ESP_RST
ESP_GPIO5
ESP_GPIO4
ESP_GPIO0
ESP_GPIO2
ESP_CS0
ESP_MISO
ESP_GPIO9
ESP_GPIO10
ESP_MOSI
ESP_SCLK

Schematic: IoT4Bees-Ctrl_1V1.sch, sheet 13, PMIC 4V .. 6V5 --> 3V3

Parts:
C1301, C1321: 10uF; C0603
L1311: 4.7uH; L2520
U1311: TPS62745DSSR; WSON-12

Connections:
+3V3: C1321.1, L1311.1, U1311.5 (VOUT); also elsewhere on the board
GND: C1301.2, C1321.2, U1311.3 (VSS), U1311.4 (EN_VIN_SW), U1311.13 (VSS), U1311.14 (VSS), U1311.G1 (VSS), U1311.G2 (VSS), U1311.G3 (VSS); also elsewhere on the board
PMIC3V3_SW: L1311.2, U1311.2 (SW)
VBAT_L: C1301.1, U1311.1 (VIN), U1311.8 (VSEL4), U1311.9 (VSEL3), U1311.10 (VSEL2), U1311.11 (VSEL1), U1311.12 (EN); also elsewhere on the board

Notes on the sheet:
PMIC 3.3V .. 10V --> 3.3V
PMIC --> 3V3
MURATA DFE252010P-4R7M=P2

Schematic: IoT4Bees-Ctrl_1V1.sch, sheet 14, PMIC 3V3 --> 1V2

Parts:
C1401: 4.7uF; C0603
C1421: 10uF; C0603
L1411: 2.2uH; L2016
U1411: TPS62743YFPR; WCSP-8

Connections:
+1V2_SMPS_PWR: C1421.1, L1411.1, U1411.2C (VOS); also elsewhere on the board
+3V3: C1401.1, U1411.2A (VIN); also elsewhere on the board
GND: C1401.2, C1421.2, U1411.1C (VSEL1), U1411.1D (VSEL2), U1411.2B (VSS), U1411.2D (VSEL3); also elsewhere on the board
PB14: U1411.1B (EN); also elsewhere on the board
PMIC1V2_SW: L1411.2, U1411.1A (SW)

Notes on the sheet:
PMIC 3.3V --> 1.2V for SMPS VDD12
PMIC --> 1V2
GPIO_SMPS_VDD12_EN
TOKO 1285AS-H-2R2M=P2
TODO: To be replaced by S-85S1A

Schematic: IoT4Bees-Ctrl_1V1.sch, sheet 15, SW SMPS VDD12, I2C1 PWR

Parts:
C1501, C1502, C1521, C1591, C1592: 100nF; C0402
TP_+1V2_MCU, TP_+3V3_I2C1: PTR1TP06R; TP06R
U1511: TS5A23166; R-PDSO-G8

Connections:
+1V2_SMPS_PWR: C1501.1, U1511.5; also elsewhere on the board
+3V3: C1502.1, U1511.1, U1511.8; also elsewhere on the board
+3V3_I2C1_PWR: C1521.1, TP_+3V3_I2C1.TP, U1511.2; also elsewhere on the board
GND: C1501.2, C1502.2, C1521.2, C1591.1, C1592.2, U1511.4; also elsewhere on the board
MCU_VDD12: C1591.2, C1592.1, TP_+1V2_MCU.TP, U1511.6; also elsewhere on the board
PA8: U1511.7; also elsewhere on the board
PB15: U1511.3; also elsewhere on the board

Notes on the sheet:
Electronic switch for: - MCU SMPS ext. 1.2V - I2C1 power 3.3V
GPIO_SW_VDD12_EN
Iq=0.01uA
GPIO_SW_I2C1_EN
SW for SMPS VDD12 PWR and I2C1 PWR

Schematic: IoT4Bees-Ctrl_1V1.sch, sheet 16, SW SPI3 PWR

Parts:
C1601: 100nF; C0402
TP_+3V3_SPI3: PTR1TP06R; TP06R
U1601: TS5A23166; R-PDSO-G8

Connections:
+3V3: C1601.1, U1601.1, U1601.5, U1601.8; also elsewhere on the board
+3V3_SPI3_PWR: TP_+3V3_SPI3.TP, U1601.2, U1601.6; also elsewhere on the board
GND: C1601.2, U1601.4; also elsewhere on the board
PB5: U1601.3, U1601.7; also elsewhere on the board

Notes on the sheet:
Electronic switch for: - SPI3 3.3V power
GPIO_SW_SPI3_EN
Iq=0.01uA
SW for SPI3 PWR

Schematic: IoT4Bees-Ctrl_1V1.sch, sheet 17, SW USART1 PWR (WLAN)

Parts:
C1701: 100nF; C0402
TP_+3V3_USART1: PTR1TP06R; TP06R
U1701: TS5A23166; R-PDSO-G8

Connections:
+3V3: C1701.1, U1701.1, U1701.5, U1701.8; also elsewhere on the board
+3V3_USART1_PWR: TP_+3V3_USART1.TP, U1701.2, U1701.6; also elsewhere on the board
GND: C1701.2, U1701.4; also elsewhere on the board
PB12: U1701.3, U1701.7; also elsewhere on the board

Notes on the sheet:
Electronic switch for: - USART1 3.3V power (WLAN)
GPIO_SW_USART1_EN
Iq=0.01uA
SW for USART1 PWR (WLAN)

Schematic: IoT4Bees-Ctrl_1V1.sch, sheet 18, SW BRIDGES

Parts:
C1801, C1802: 100nF; C0402
TP_+3V3_BRIDGES: PTR1TP06R; TP06R
U1801: TS5A23166; R-PDSO-G8

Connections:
+3V3: C1801.1, U1801.1, U1801.5, U1801.8; also elsewhere on the board
+3V3_BRIDGE_PWR: C1802.1, TP_+3V3_BRIDGES.TP, U1801.2, U1801.6; also elsewhere on the board
GND: C1801.2, C1802.2, U1801.4; also elsewhere on the board
PC4: U1801.3, U1801.7; also elsewhere on the board

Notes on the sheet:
Electronic switch for: - 2x Bridges power 3.3V
GPIO_SW_BRIDGE_EN
Iq=0.01uA
SW for Bridges PWR and spare

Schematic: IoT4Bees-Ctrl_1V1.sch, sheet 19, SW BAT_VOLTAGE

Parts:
C1901, C1902: 100nF; C0402
TP_BAT_VOLTAGE1: PTR1TP06R; TP06R

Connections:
+3V3: C1902.1; also elsewhere on the board
+3V3_BRIDGE_PWR: C1901.1; also elsewhere on the board
+BAT_VOLTAGE_PWR: TP_BAT_VOLTAGE1.TP; also elsewhere on the board
GND: C1901.2, C1902.2; also elsewhere on the board

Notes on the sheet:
Electronic switch for: - 2x Bridges power 6V
Iq=0.01uA
GPIO_SW_VOLTAGE_EN
SW for Bridges PWR and spare
TODO: add SL54059 10 Ld 3x3 TDFN

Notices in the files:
CAD/Eagle/IoT4Bees-Ctrl_1V1.brd:
(C) 2019
